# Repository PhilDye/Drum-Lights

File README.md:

# Drum Lights

## About

This project provides synchronised, colour-changing, remote-control LED lights for a drum band (but could be used for other similar applications). It was first created for [Swan Samba](https://www.swansamba.co.uk) to use for evening/winter performances.

Hundreds of hours have gone into developing this project - if you make use of it and wish to thank me, then please consider a donation;

Contributions to improve this documentation or code would also be very welcome to help other users.

## Skills & Requirements

This is a technically complex project! Whilst I've partly documented it here, to use it successfully you'll need to improvise a bit and will need some experience with;

- sourcing and assembling the electronic components (eg from AliExpress), including soldering techniques

- building and uploading the firmware using [Visual Studio Code](https://code.visualstudio.com/) and [PlatformIO](https://platformio.org/)

- 3D-printing for the enclosure boxes

If you are not confident with these skills, then this probably isn't the project for you; I'm happy to answer the odd question, but this project is provided 'as-is' and as a hobby I'm unable to provide extensive support, sorry!

## Overview

The system consists of three parts;

- Transmitter (TX) - receives commands from a controller and broadcasts a radio signal to the receivers.

- Receiver (RX) - receives the broadcast radio signal and drives a strip of individually-addressable LED pixels mounted inside the shell of each drum.

- Controller - the phone used to pick colours/patterns. On an iPhone this is the native [iOS app](#ios-app) over Bluetooth LE; on anything else (or as a fallback) it's the [web UI](#web-ui-fallback) served by the TX over its own WiFi hotspot. Both can be used at once and stay in sync.

Both TX and RX are powered by portable USB battery packs ('power banks'), typically carried in a pocket by each band member (or could be mounted to each drum).

## Transmitter

The transmitter (TX) consists of an ESP32-S3 dev-kit board plus a RF24-based radio module, mounted on proto-board. The original design used a classic ESP32 dev-kit; that build is still supported (web UI only, see below) but new transmitters should use the S3, because the classic ESP32's Bluetooth connects too slowly and unreliably for live use (see #19).

Although the RF24 modules use the 2.4Ghz ISM radio band, they are not WiFi; this was chosen for low-latency and avoiding the need for a network router for a large number of receivers (which would not be able to connect simultaneously to the ESP32 hotspot).

Significantly better results have been found with the E01-2G4M27D module, rather than the cheaper basic nRF24L01-PA-LNA which suffers RF interference and instability.

The RF24 module uses a configurable transmit power with multiple channels available, but does not avoid packet collision with other sources using the same frequency. For this reason we retransmit each command multiple times in quick succession, in the hope that 'one gets through'. It also requires a stable 3.3v supply, which at high-power transmission could exceed that available from the ESP32, so a separate buck converter is used fed from the power supply.

The TX offers two ways in for controllers, both feeding the same single mode-change path so every controller sees the same state;

- **Bluetooth LE** (ESP32-S3 only): a GATT service used by the iOS app, with State (read/notify), Command (encrypted, authenticated write) and Info (protocol, firmware and catalogue versions) characteristics. Phones pair once with a 6-digit PIN. Up to four controllers can be connected at once and eight pairings are remembered (the oldest is dropped when full). The full protocol is in [iOS/DESIGN.md](iOS/DESIGN.md).

- **WiFi hotspot + web UI**: the ESP32 broadcasts a WiFi hotspot (configured as a captive portal) running an AsyncWebServer that serves a HTML/CSS/JS page from LittleFS, with commands and state carried over a websocket at `ws://192.168.4.1/ws`.

The available effects and colours are defined once in [`TX/app/src/modes.json`](TX/app/src/modes.json). The web UI is rendered from it, the iOS app bundles a copy, and the TX reports its catalogue version so the app can warn about a mismatch. CI fails if the copies drift apart.

### Building the TX firmware

There are two PlatformIO environments in `TX/platformio.ini`:

- `esp32-s3` (default): an ESP32-S3 dev-kit (8MB or 16MB flash), with the web UI **and** the Bluetooth LE service. The RF24 goes on the S3's default SPI pins: SCK 12, MISO 13, MOSI 11, CS 10, CE 9. Serial is on the native USB port; if your cable is in the UART (COM) port, delete `-DARDUINO_USB_CDC_ON_BOOT=1` or the monitor stays silent.
- `az-delivery-devkit-v4`: the original classic ESP32 TX, web UI only (RF24 on SCK 18, MISO 19, MOSI 23, CS 5, CE 17).

Create `TX/src/secrets.h` (it's git-ignored):

```cpp
#define WIFI_SSID "Drum Lights"
#define WIFI_PASS "your-wifi-password"
#define BLE_PASSKEY 482916          // 6-digit Bluetooth PIN; no leading zero
// #define BLE_NAME "Swan Samba TX" // optional, so neighbouring bands don't collide
```

`BLE_PASSKEY` is required for the S3 build; it won't compile without it.

Then build the web UI into `TX/data` and upload both the filesystem and the firmware:

```sh
cd TX/app
npm ci
npm run build              # writes TX/data
cd ..
pio run -t uploadfs        # LittleFS image with the web UI
pio run -t upload          # firmware
```

Add `-e az-delivery-devkit-v4` to the `pio` commands for a classic ESP32 TX.

**Hold the BOOT button for 5 seconds** to forget every Bluetooth pairing (the LED flashes three times), e.g. after losing a phone. Paired iPhones then need "Forget This Device" in their Bluetooth settings before they can pair again.

## Controlling the lights

### iOS app

The native iPhone app in [`iOS/`](iOS/README.md) is the preferred controller. It talks to the TX over Bluetooth LE, so the phone keeps its normal internet connection and never has to join the hotspot. It also gives things the web page can't:

- haptic confirmation of each tap, so the operator can keep their eyes on the band;
- staying connected with the screen locked, and reconnecting by itself when the TX comes back into range;
- remembering "its" TX, so it won't grab a neighbouring band's transmitter.

The app shows "Sent to TX" rather than "Delivered": the TX confirms it accepted a command, but nothing can confirm the drums received it. While disconnected the controls dim and ignore taps, rather than queuing stale commands.

Currently the Live tab and Settings work. Saved palettes, Live Activity / lock-screen controls, App Intents (Action Button, Shortcuts) and Apple Watch are planned; see [iOS/DESIGN.md](iOS/DESIGN.md) and #20. Build and test instructions are in [iOS/README.md](iOS/README.md). It needs iOS 17 or later; in the Simulator it drives a pretend TX.

### Web UI (fallback)

The web UI remains a first-class controller for Android phones, anyone without the app, and for classic-ESP32 transmitters that have no Bluetooth. Connect to the TX's WiFi hotspot and the captive portal opens the control page (or browse to `http://192.168.4.1`).

The iOS app can also fall back to it: with *Settings › WiFi fallback* turned on, if Bluetooth hasn't connected within 6 seconds the app joins the hotspot itself and uses the same websocket, then leaves again once Bluetooth is back. This needs the Hotspot Configuration capability, which requires a paid Apple Developer Program membership.

The trade-offs of the web UI are the reason the app exists: the phone loses its internet while on the hotspot, iOS may nag about "no internet connection", and the connection drops when the screen locks.

## Receiver

The receiver (RX) consists of an ESP8266-based Wemos D1-mini clone board, plus a RF24 module, mounted on a PCB.

Better reliability has been found with the E01-ML01DP4 module, rather than the cheaper basic nRF24L01. 

It receives radio commands from the TX and uses these to drive a strip of WS2812B LEDs ("neopixels") using the excellent [FastLED](https://fastled.io) library.

Best-practice often requires the use of a 3.3v level-shifter and/or resistor in the data line, but testing showed this not to be neccessary, probably given the short data-line length, although a capacitor _is_ provided on the power supply (although as a DC source, USB battery packs are probably sufficiently stable already). 

The receiver reads a configuration file with the number of LEDs available in the attached strip, and uses this to dynamically compute moving effects to suit the varying drum sizes within a band. This file should be uploaded to the filesystem on each board.

## LED mounting

Self-adhesive IP65 WS2812B LED strip is mounted inside the shell of each drum, approx a quarter of the way from the top, around the full circumference. 

The strip requires 3-core cable: 5V, data and ground;

Ensure this is sealed with silicone or hot-glue to prevent water ingress, and insulated with heatshrink;

The cable exits through the sound hole/port and runs to an enclosure holding the RX board.

## Enclosures

Both RX and TX are mounted in custom 3D-printed boxes; the RX in particular is designed to secure the components against vibration. Power is supplied via a 5.5mm DC jack using a [USB cable](https://www.kenable.co.uk/en/usb-cables-adapters/usb-20-cables/usb-20-adapters/7629-usb-to-dc-power-cable-usb-20-for-21mm-x-55mm-5v-2a-2000ma-1m-007629-5055383476299.html).

Current designs are in [`STL/`](STL/) as FreeCAD sources plus printable STL/STEP files: the v4.1 RX box and lid, the original (2023) TX box for the classic ESP32, and the v5 TX box and lid for the ESP32-S3.

Experience has shown it's best to mount the RX on the *rear* of all drums with 3M VHB double-sided tape. Ensure the TX is positioned at the rear of the band too, to avoid metal-shelled drums blocking the RF signal. _Ensure players know this to mount their drum accordingly!_

## PCBs

After breadboard prototyping, initial builds were built on protoboard but for more than a small handful of boards (which require plenty of soldering!), it's advisable to consider custom-printed PCBs. 

[Design files are provided](PCB/) for [KiCAD](https://www.kicad.org/) with Gerber output files ready for use at [JLCPCB](https://jlcpcb.com/). The PCB is for the RX only; the TX (either board) is built on proto-board.

## Effects

The lighting patterns currently available are;

- Static: every pixel the same colour, available in various colours.
- Chase: 4 quadrants of moving pixels with a fading 'tail', rotating around the drum, available in various colours.
- Twinkle: a number of pixels randomly light then fade, available in various colours.
- Fire: a 'flickering' flame effect in varying colours.
- 'Rio Spin': 3 segments of solid colour (blue/green/yellow) rotating around the drum.
- 'Rio Disco': twinkle, with blue/green/yellow only.
- 'Rio Flag': a blue/green/yellow sequence representing the Brazilian flag, rotating around the drum.
- Rainbow: a classic FastLED multi-colour effect, rotating around the drum.
- Hazards: 2 segments of orange at the side of each drum, designed to imitate a vehicle's hazard lights when stopped.
- Strobe: rapid, short-duration flashes of full-intensity white - perfect for big hits!
- 999: alternate high-frequency flashing blue strobes (named after the UK emergency-services telephone number).
- Auto: randomises most of the above every 30s; ideal to 'fire-and-forget' if no-one is available to run the show.

Many of the FastLED demo effects suit 1D (strip) or 2D (panel) setups; the circular/ring configuration here does present some additional challenges, but further effects are really only limited by imagination (although compexity of the control UI should be considered).

## Synchronicity

Currently, all drums receive the same command and hence display the same colour/pattern at the same time. The speed of the rotating patterns (ie RPM) is not synchronised across varying diameter drums; early experiments showed this to be hard to maintain a smooth frame rate at slower speeds (on smaller drums); temporal dithering may help this.

It would be relatively simple to use addressing or channel features of the RF24 to control each drum type seperately, allowing complex displays and patterns 'across' the band. The main obstacle is likely to be the complexity of the control UI.

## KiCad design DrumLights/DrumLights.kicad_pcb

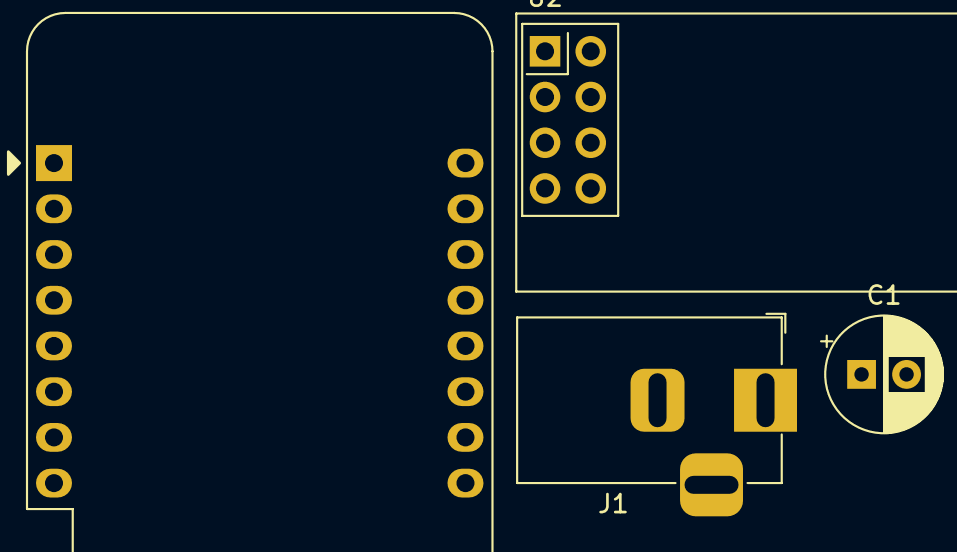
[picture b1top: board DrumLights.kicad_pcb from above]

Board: 2 copper layers, 4 parts (0 on the bottom side), 3 nets, no tracks yet.

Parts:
C1: C_Polarized_US; CP_Radial_D6.3mm_P2.50mm
J1: Barrel_Jack_Switch; BarrelJack_Horizontal
U1: WeMos_D1_mini; WEMOS_D1_mini_light
U2: NRF24L01_Breakout; nRF24L01_Breakout

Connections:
unnamed: U1.8 (3V3), U2.2 (VCC)
unnamed: C1.1, J1.1, U1.9 (5V)
unnamed: C1.2, J1.2, U1.10 (GND), U2.1 (GND)

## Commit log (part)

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2022-10-08 Combine RX and TX repos
2022-10-08 Basic gitignore
2022-10-13 Switch to match hardware
2022-10-13 Show better error on radio error
2022-10-13 Radio changes to support multiple RXs
2022-10-13 Strobe mode!
2022-10-13 Size for largest drum
2022-10-13 change address
2022-10-13 Send TX three times for reliability
2022-10-14 Support for strobe
2022-10-14 Support for toggle off
2022-10-14 Fix strobe crashing in twinkle
2022-10-14 Add hazards
2022-10-16 Config file for number of LEDs
2022-11-06 Use a constant for retransmits
2022-11-06 Filesystem for config and web UI (#1)
    * WIP
    * Switch to match hardware
    * Show better error on radio error
    * Radio changes to support multiple RXs
    * Strobe mode!
    * Size for largest drum
2022-11-07 Add README
2022-11-25 Increase radio robustness
2022-11-25 Favicon for desktop app shortcut
2022-11-25 Alert on lost websocket
2022-11-26 Off button instead of toggle to allow re-sending
2023-11-05 chore: rename a few things
2023-11-05 feat: add auto-randomm for unattended use
2024-09-05 PCB design
2024-09-05 wip: photos
2024-09-05 fix: type cast warnings
2024-09-05 feat: blue strobes
2024-09-05 feat: optimisations
2024-09-08 chore: add editorconfig
2024-09-08 feat: remote OTA
2024-09-08 feat: use default `fill_solid`
2024-09-08 chore: formatting
2024-09-08 feat: param renames, type changes, status pixel changes
2024-09-08 chore: remove OTA
2024-09-08 feat: fire
2024-09-17 feat: improve status and add orange
    commit 50e533feae007a89972b5c5836e0d8f8052f43fb
    Author: Phil Dye <phil@phildye.org>
    Date: Tue Sep 17 20:58:13 2024 +0100
    feat: add orange
    commit 84422e6047ac221cc4507d9b890e7efa47c629d0
    Author: Phil Dye <phil@phildye.org>
2024-09-17 fix: default state
2024-09-17 feat: default to blue chase after power-on idle
    allows drums to operate without the TX
2024-09-17 chore: remove config from repo
2024-09-22 feat: add TX new modes
2024-09-22 chore: deps update
2024-09-22 fix: random auto initialiser
2024-09-23 feat: re-layout TX to fit new things in
2024-09-25 refactor: types
2024-09-25 refactor: split files
2024-09-25 feat: tricolor twinkle
2024-09-25 feat: bicolor chase
2024-09-25 feat: christmas
2024-09-25 refactor: rioDisco uses twinkle
2024-09-25 fix: prevent overflow
2024-09-25 feat: ukraine
2024-09-25 feat: SaintsFC 😂
2024-09-25 refactor: default params
2024-09-25 feat: change default
2024-09-25 chore: use correct board
2024-10-13 feat: portal rewrite, Bootstrap tabbed interface
2024-10-13 refactor: clarify method names
2024-10-13 feat: replace deprecated spiffs with littlefs
2024-10-13 refactor: networking for better captive portal
2024-10-13 fix: remove redundant class
2024-10-13 feat: use stronger button for strobe
2024-10-13 chore: remove commented code
2024-10-13 fix: type
2024-10-13 fix: close ini file
2024-10-13 fix: major 🐛 with reading payload
    Not quite sure what was happening here, but reading unsigned `int` straight into signed `ledMode`?
2024-10-13 chore: dependency updates
2024-10-13 fix: red fire wasn't red
2024-11-08 fix: modal not hiding on reconnect
2024-11-10 fix: missing semicolons
2024-11-10 chore: delete build output
2024-11-10 docs: improved, with pics
2024-11-10 chore: resize images
2024-11-10 doc: updates
2025-07-09 Initial plan
2025-07-09 Add configurable RF channel support to avoid WiFi interference
2025-07-09 Update README with RF channel configuration documentation
2025-07-10 Add rotation direction configuration and update affected functions
2025-07-10 Add validation for rotation direction configuration
2025-10-11 fix: typo
2025-10-11 feat: add 3d print files
2026-05-17 feat(TX): replace 5x burst with 100ms heartbeat + zero-latency edge sends
    TX now continuously rebroadcasts CurrentMode at 10 Hz so receivers
    self-heal from lost packets and late joiners catch up within one
    interval. UI mode changes still send immediately for zero perceptible
    latency. Mode 98 (strobe) is a single-packet transient that bypasses
    CurrentMode so the heartbeat never holds it. Also fixes a latent
    assignment-vs-comparison bug in the AUTO-mode revert path.
2026-05-17 fix(TX): correctly detect AUTO mode exit (use autoDelay.isRunning)
    The Task 1 commit (6688ddb) replaced an assignment-vs-equality bug
    (CurrentMode = AUTO_MODE) with previousMode == AUTO_MODE, but
    CurrentMode never actually holds AUTO_MODE (-1) at this point: the
    AUTO branch overwrites newMode with a real pattern value before
    assigning it to CurrentMode. The previousMode predicate therefore
    never fired, leaving autoDelay running forever and yanking the drum
2026-05-17 feat(rx): add custom INI parser for LittleFS config
2026-05-17 feat(RX): idempotent receive + self-contained 5-flash strobe
    readRadio() now only mutates state when the received mode differs from
    the running one, so the new TX heartbeat (10 Hz duplicates of the
    current mode) does not disrupt running patterns. case 98 produces all
    5 strobe flashes from a single received packet, since TX no longer
    bursts.
2026-05-17 feat(rx): add one-shot SPIFFS to LittleFS migration helper
2026-05-17 feat(rx): switch from SPIFFS to LittleFS with first-boot migration
